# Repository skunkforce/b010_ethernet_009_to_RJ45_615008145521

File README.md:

# edgy_board number b010
This design is part of the [edgy board project](https://github.com/skunkforce/edgy_boards).

# getting started
This repository uses submodules. After cloning use the command 

```$ git submodule update --init --recursive```

to pull the submodules before opening the project with kicad. 

# Tests
Tests can be found in [TESTS.md](TESTS.md)

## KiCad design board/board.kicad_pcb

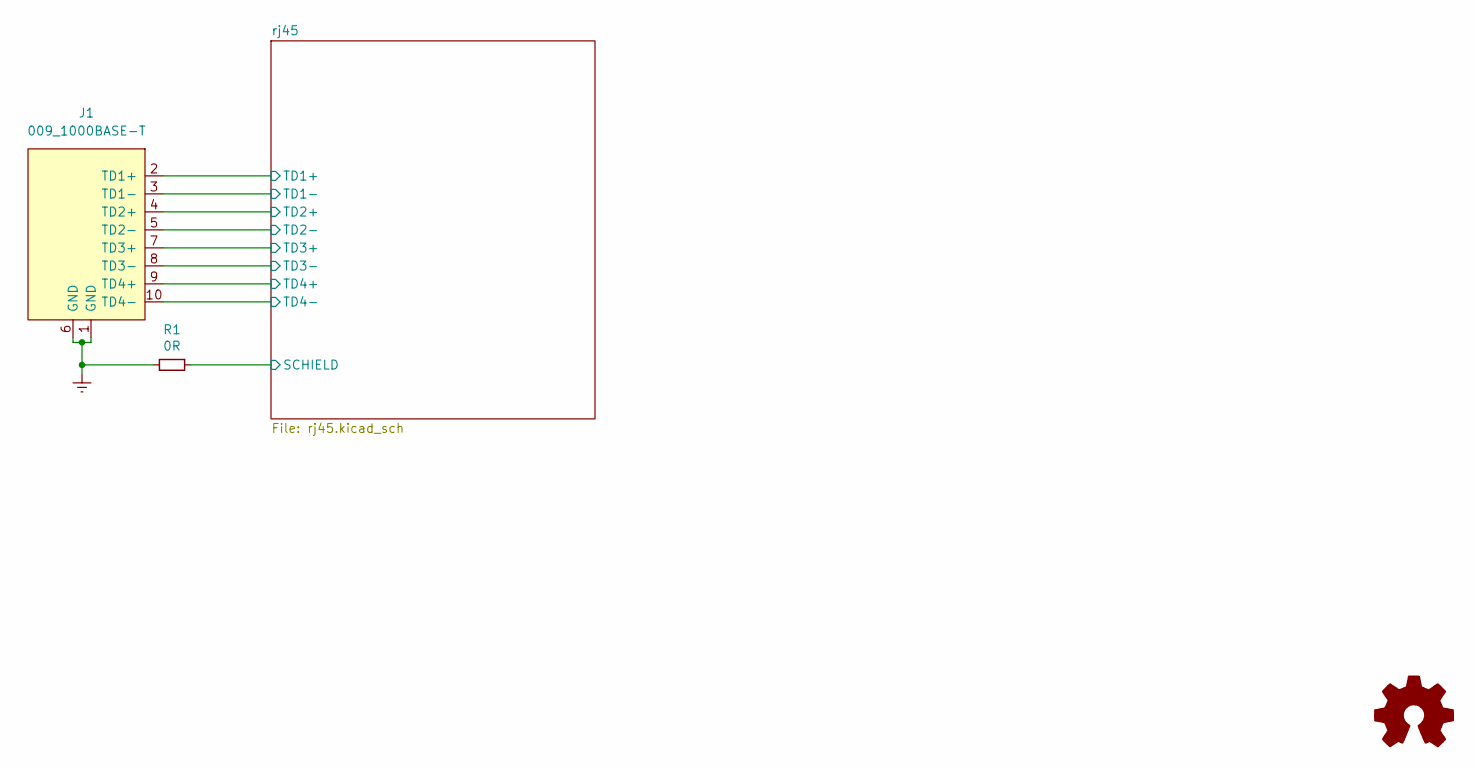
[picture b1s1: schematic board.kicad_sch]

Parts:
J1: 009_1000BASE-T; on_edge_2x05_device
LOGO1: Logo_Open_Hardware_Small; OSHW-Symbol_6.7x6mm_SilkScreen
R1: 0R; R_0603_1608Metric

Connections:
/rj45/SCHIELD: R1.1; also elsewhere on the board
/rj45/TD1+: J1.2 (TD1+); also elsewhere on the board
/rj45/TD1-: J1.3 (TD1-); also elsewhere on the board
/rj45/TD2+: J1.4 (TD2+); also elsewhere on the board
/rj45/TD2-: J1.5 (TD2-); also elsewhere on the board
/rj45/TD3+: J1.7 (TD3+); also elsewhere on the board
/rj45/TD3-: J1.8 (TD3-); also elsewhere on the board
/rj45/TD4+: J1.9 (TD4+); also elsewhere on the board
/rj45/TD4-: J1.10 (TD4-); also elsewhere on the board
Earth: J1.1 (GND), J1.6 (GND), R1.2

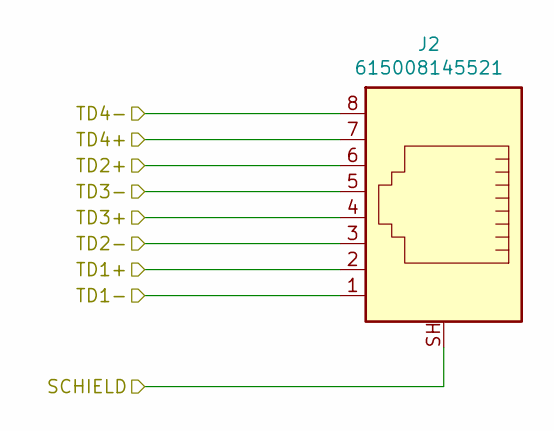
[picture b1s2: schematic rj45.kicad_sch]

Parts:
J2: 615008145521; RJ45_Wuerth_615008145521_Horizontal; MPN 615008145521

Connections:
/rj45/SCHIELD: J2.SH; also elsewhere on the board
/rj45/TD1+: J2.2; also elsewhere on the board
/rj45/TD1-: J2.1; also elsewhere on the board
/rj45/TD2+: J2.6; also elsewhere on the board
/rj45/TD2-: J2.3; also elsewhere on the board
/rj45/TD3+: J2.4; also elsewhere on the board
/rj45/TD3-: J2.5; also elsewhere on the board
/rj45/TD4+: J2.7; also elsewhere on the board
/rj45/TD4-: J2.8; also elsewhere on the board

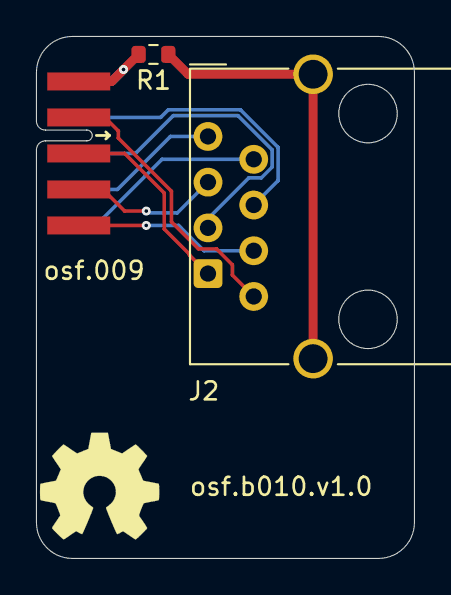
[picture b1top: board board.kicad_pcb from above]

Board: 2 copper layers, 21.0 x 29.0 mm, 4 parts (0 on the bottom side), 10 nets.

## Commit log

2023-02-23 initial
2023-02-27 fixed silkscreen
2023-03-01 updated put_on_edge submodule
2023-03-02 moved tracks for better EMC
2023-03-04 updated submodule
